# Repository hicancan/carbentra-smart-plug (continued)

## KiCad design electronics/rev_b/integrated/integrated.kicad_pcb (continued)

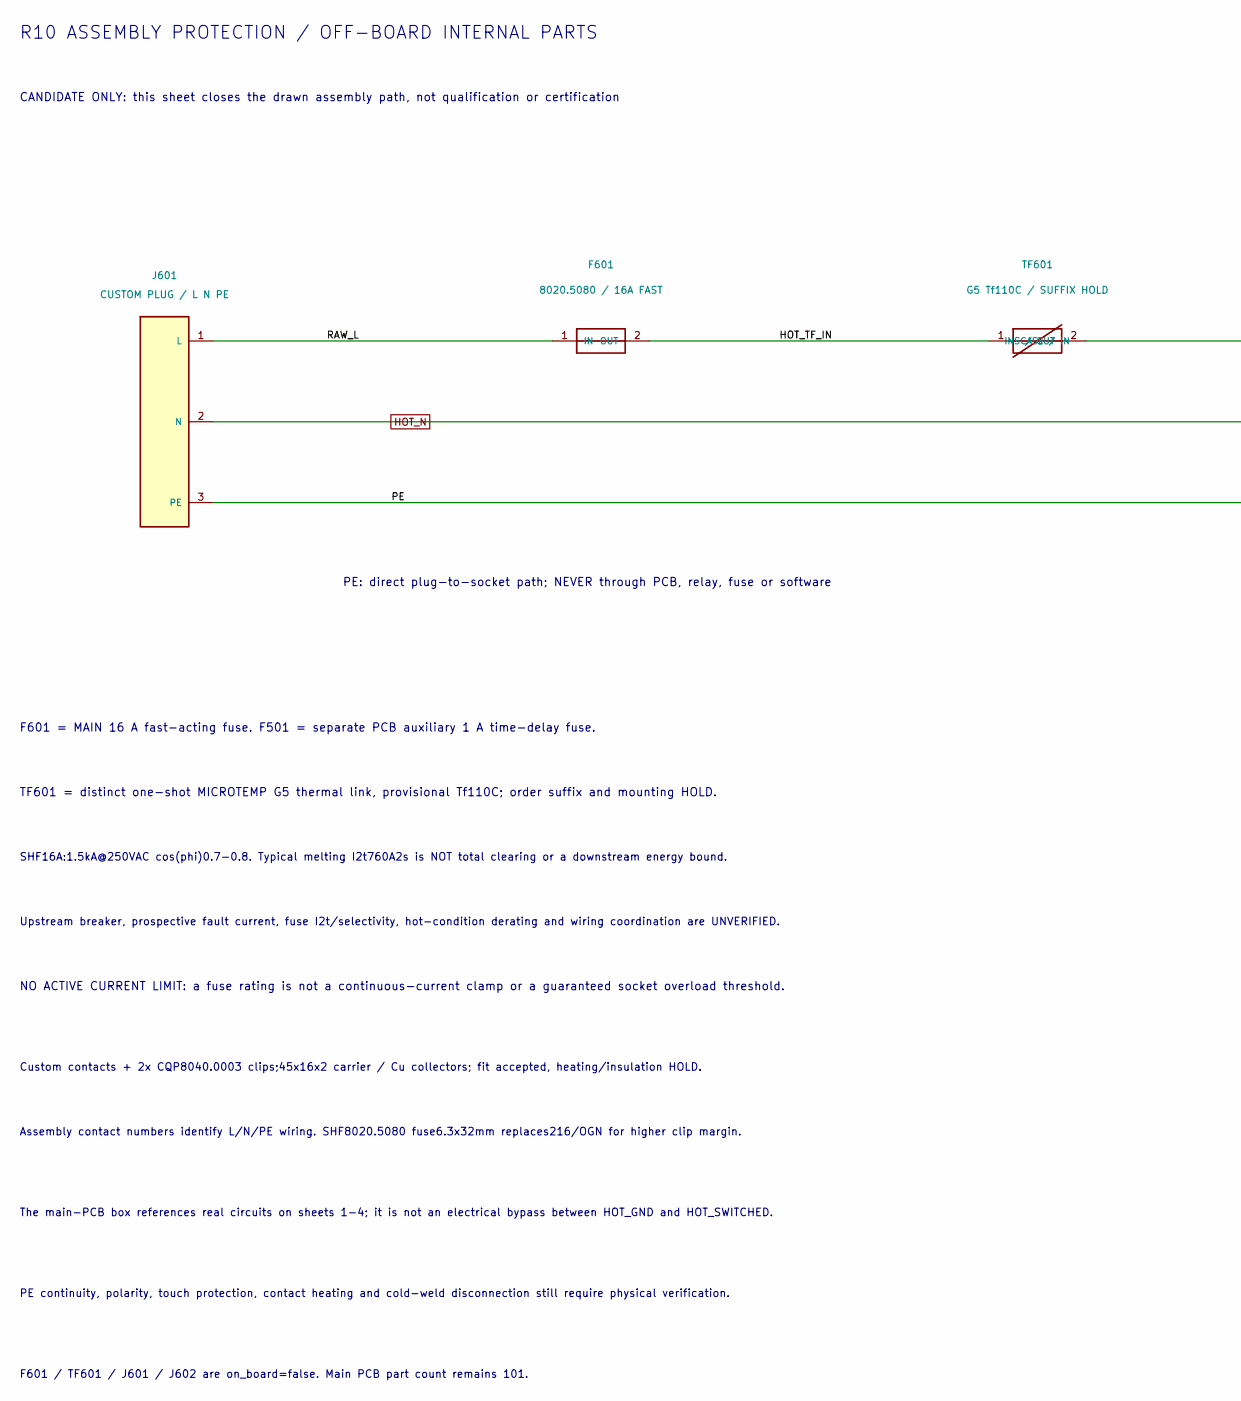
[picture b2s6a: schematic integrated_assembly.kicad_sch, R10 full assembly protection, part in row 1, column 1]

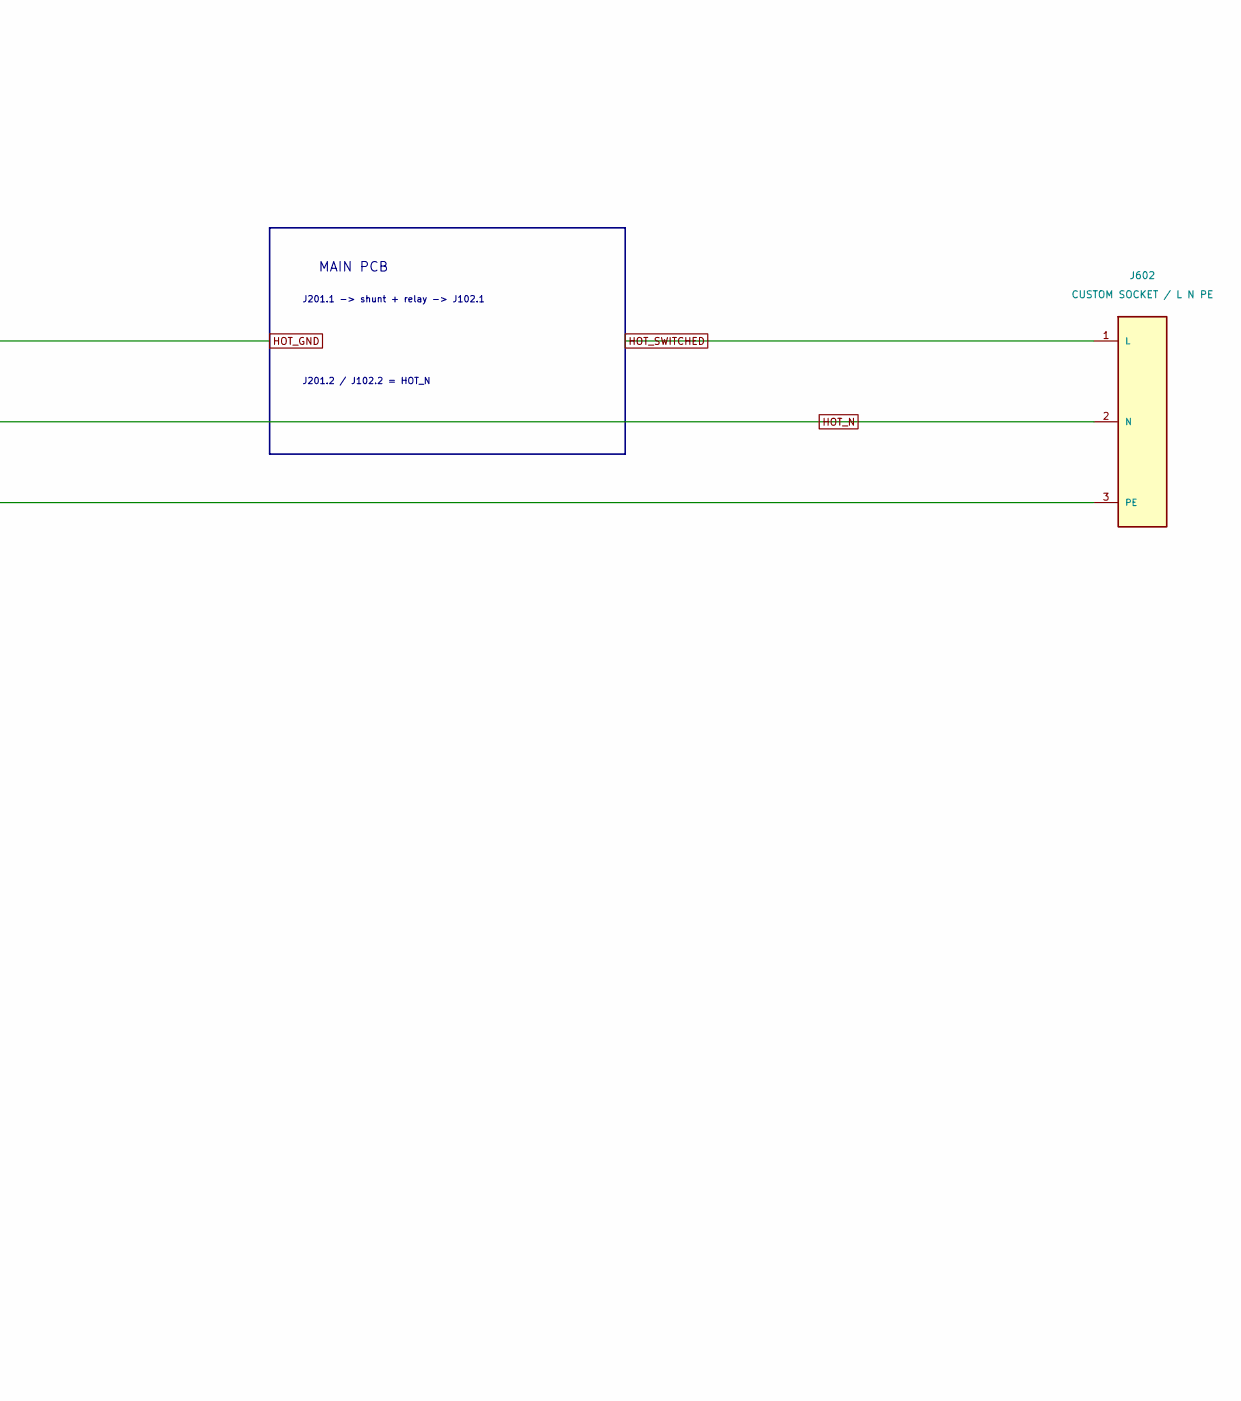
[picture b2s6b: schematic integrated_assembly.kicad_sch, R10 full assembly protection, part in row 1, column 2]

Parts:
F601: 8020.5080 / 16A FAST
J601: CUSTOM PLUG / L N PE
J602: CUSTOM SOCKET / L N PE
TF601: G5 Tf110C / SUFFIX HOLD

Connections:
unnamed: F601.1 (IN), J601.1 (L)
unnamed: F601.2 (OUT), TF601.1 (CASE / IN)
unnamed: J601.2 (N), J602.2 (N)
unnamed: J601.3 (PE), J602.3 (PE)

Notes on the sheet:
R10 ASSEMBLY PROTECTION / OFF-BOARD INTERNAL PARTS
CANDIDATE ONLY: this sheet closes the drawn assembly path, not qualification or certification
MAIN PCB
J201.1 -> shunt + relay -> J102.1
J201.2 / J102.2 = HOT_N
PE: direct plug-to-socket path; NEVER through PCB, relay, fuse or software
F601 = MAIN 16 A fast-acting fuse. F501 = separate PCB auxiliary 1 A time-delay fuse.
TF601 = distinct one-shot MICROTEMP G5 thermal link, provisional Tf110C; order suffix and mounting HOLD.
SHF16A:1.5kA@250VAC cos(phi)0.7-0.8. Typical melting I2t760A2s is NOT total clearing or a downstream energy bound.
Upstream breaker, prospective fault current, fuse I2t/selectivity, hot-condition derating and wiring coordination are UNVERIFIED.
NO ACTIVE CURRENT LIMIT: a fuse rating is not a continuous-current clamp or a guaranteed socket overload threshold.
Custom contacts + 2x CQP8040.0003 clips;45x16x2 carrier / Cu collectors; fit accepted, heating/insulation HOLD.
Assembly contact numbers identify L/N/PE wiring. SHF8020.5080 fuse6.3x32mm replaces216/OGN for higher clip margin.
The main-PCB box references real circuits on sheets 1-4; it is not an electrical bypass between HOT_GND and HOT_SWITCHED.
PE continuity, polarity, touch protection, contact heating and cold-weld disconnection still require physical verification.
F601 / TF601 / J601 / J602 are on_board=false. Main PCB part count remains 101.

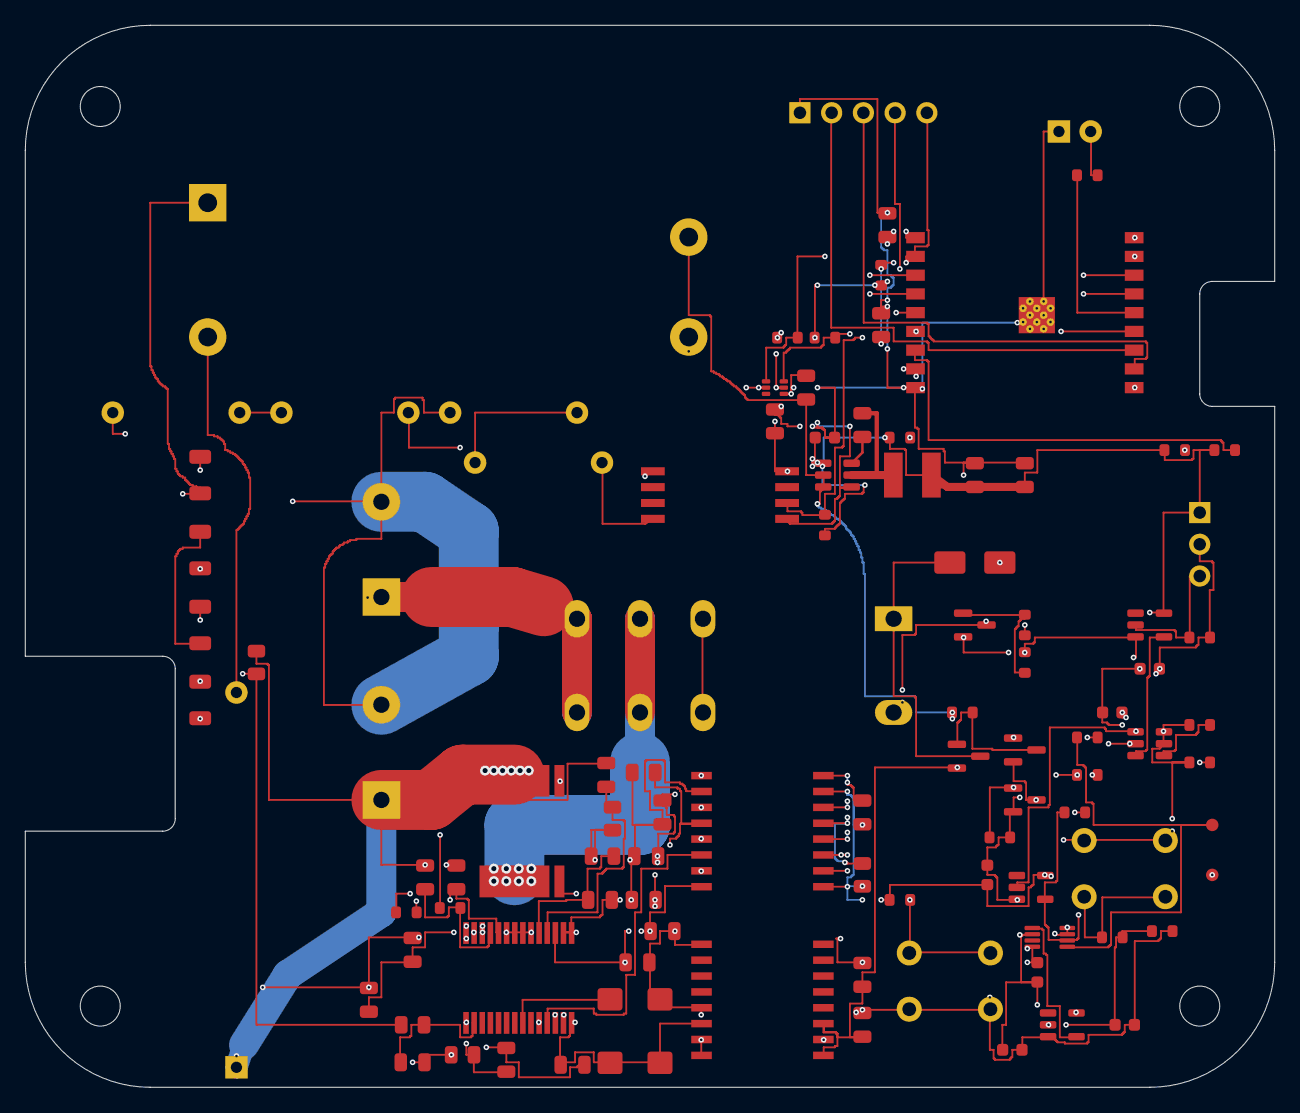
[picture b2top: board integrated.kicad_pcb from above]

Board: 4 copper layers, 100.0 x 85.0 mm, 105 parts (1 on the bottom side), 66 nets.

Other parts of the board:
H1, H2, H3, H4: MountingHole_3.2mm_M3

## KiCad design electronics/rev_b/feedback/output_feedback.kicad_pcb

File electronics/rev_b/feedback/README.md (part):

# Rev B isolated post-switch output detector

**Development candidate. Do not fabricate, connect to mains, or treat any signal as a safety indication.** Baseline EVT-A files were not edited. This is a separate, routed Rev B source module, not a certified socket or a release to energize.

## Result and interface

A 35 × 25 × 1.6 mm, two-layer module senses differential voltage at the **actual output socket L and N contacts**, after every switched pole. It uses a full-wave AC-input threshold optocoupler, four protective-impedance resistors and isolated 3.3 V logic. It needs one MCU GPIO capable of observing pulses, plus isolated power and ground. No load current is required.

- J1: L_POST, socket-side line sense only
- J2: N_POST, socket-side neutral sense only
- J3.1: +3V3_ISO; J3.2: GND_ISO; J3.3: OUTPUT_PRESENT_N
- Logic: recurring active-low pulses at twice mains frequency; LOW by itself is not a complete measurement
- Reserve **9 mm above PCB, 3 mm below PCB**, plus mating connector and wire bend/strain-relief space. These are keepout reservations, not a validated complete assembly envelope
- No protective earth conductor or load-current path is routed on this module

`output_feedback.kicad_sch`, `.kicad_pcb`, `.kicad_pro`, `.kicad_dru`, `Feedback.kicad_sym`, `Feedback.pretty/`, `pin_net_manifest.json` and `bom.csv` are the design sources. `exports/` contains schematic and board-review SVG/PNG plus the exported KiCad netlist. `scripts/build_feedback.py` rebuilds the source; `scripts/verify_feedback.py` independently checks connectivity, domain spacing and calculations. No Gerbers or fabrication package is provided.

## Circuit and pin correctness

The implemented signal path is:

L_POST → R1 33 kΩ → R2 33 kΩ → U1 pin 1 (AC1)

N_POST → R4 33 kΩ → R3 33 kΩ → U1 pin 4 (AC2)

U1 is **Broadcom ACPL-K376-560E**. Its internal bridge and input threshold controller feed the optical isolation stage. Pin 8 is isolated VCC, pin 5 isolated GND, pin 6 open-collector output. Pins 2 (DC+), 3 (DC−), and 7 (NC) are intentionally unconnected. R5, 1.8 kΩ, pulls pin 6 to isolated 3.3 V; C1, 100 nF, bypasses its isolated supply. There is no rectifier storage capacitor or mains-to-MCU resistive divider.

The source pin table was visually checked against the manufacturer functional diagram, not inferred from a generic optocoupler symbol. The four resistors are split across both input legs; **neither leg is considered touch-safe or guaranteed neutral**. Their intermediate nodes remain in the primary domain. [Broadcom datasheet, pp. 1–2](https://docs.broadcom.com/doc/AV02-2153EN)

## Why this topology

Three options were compared:

1. **H11AA1 AC phototransistor:** simple and naturally reverse-protected. However, its minimum CTR is 20% at ±10 mA, VCE = 10 V, 25°C. That is not a guarantee at ~1–2 mA, hot, aged, or saturated. At 198 VAC, obtaining 10 mA at the crest requires about 27.85 kΩ or less; at 264 VAC the resistor loss is then approximately 2.50 W before tolerance. Unnecessarily hot for a compact socket. [Vishay H11AA1 datasheet](https://www.vishay.com/docs/83608/h11aa1.pdf)
2. **Discrete 1000 V bridge + VO615A-4 phototransistor:** the 56% minimum CTR at 1 mA is useful, but it is specified at VCE = 5 V and 25°C. Multiplying that CTR into a saturated 3.3 V GPIO interface would overstate the guarantee. A transistor solution requires separate low-VCE/temperature/aging qualification or an appropriately biased comparator design. [Vishay VO615A datasheet](https://www.vishay.com/docs/81753/vo615a.pdf)
3. **Selected ACPL-K376 integrated bridge + threshold optocoupler:** threshold detection occurs before the optical transfer path, so the detector is specified by input threshold limits rather than a guessed CTR minimum. The manufacturer covers −40…105°C and includes 3.3 V operation. The component isolation ratings do not certify this PCB or assembly. [Broadcom datasheet, electrical tables](https://docs.broadcom.com/doc/AV02-2153EN)

This choice still contains a bridge and optocoupler; the bridge is integrated. There is no external diode footprint that can be assembled with the wrong AC/DC pin order.

## Component candidates and footprint basis

| Ref | Candidate | Mechanical/footprint basis |
|---|---|---|
| U1 | ACPL-K376-560E | Manufacturer SSO-8, custom `Feedback:SSO8_ACPL_K376`; body 6.807 ±0.127 × 5.850 ±0.50 mm, max height 3.307 mm; 1.27 mm pin pitch; lead span 11.50 ±0.25 mm |
| R1–R4 | Vishay PR01000103302FA100 | PR01, 33 kΩ, ±1%, 1 W at 70°C, 350 V working-voltage ceiling; custom horizontal 10.16 mm pitch, 0.9 mm drills; max body 6.5 × 2.5 mm; 0.58 ±0.05 mm leads; assembly standoff/lead forming still to qualify |
| R5 | Yageo RC0603FR-071K8L | 1.8 kΩ ±1%, 1608 metric; KiCad 0603 footprint; ordinary isolated-side pullup |
| C1 | Murata GRM188R71C104KA01D | 100 nF ±10%, X7R 16 V, 1608 metric; KiCad 0603 footprint |
| J3 | Samtec TSW-103-07-G-S | 2.54 mm pitch, three 0.635 mm square pins; vertical 1×3 header footprint; 5.84 mm mating post + 2.54 mm body = 8.38 mm nominal above board |
| J1, J2 | Internal insulated wire solder lands | Custom 1.2 mm drill / 2.4 mm copper diameter; **final wire gauge, insulation, anchoring and strain relief remain HOLD**, not a rated detachable mains connector |

U1's custom pads are 1.905 × 0.65 mm, with opposed pad centers 10.745 mm apart. The resulting pad-edge distance is 8.84 mm; the 0.65 mm width follows a practical KiCad SSO-8 land width, wider than the maximum 0.511 mm component lead. The 12.65 mm outer land span follows the manufacturer drawing. A 1 mm wide, 21 mm long routed slot under the package provides extra surface-contamination margin. **This is not permission to reduce air clearance.**

PR01 has a non-flammable coating and documented active/passive flammability tests; it is **not an agency-qualified safety fuse in this use**, and an unspecified benign open-circuit failure is not assumed. Its power/voltage/pulse/load-temperature limits all apply. [Vishay PR01 family datasheet](https://www.vishay.com/docs/28729/pr010203.pdf), [Samtec exact header](https://www.samtec.com/products/tsw-103-07-g-s), [Murata exact capacitor](https://www.murata.com/en-us/products/productdetail?partno=GRM188R71C104KA01D)

## Worst-case electrical calculations

The target is sinusoidal **198–264 VAC, 50/60 Hz**. Distorted/phase-cut waveforms require separate tests. This detector is not an RMS voltmeter. All numbers below are calculations, not bench measurements.

RΣ = 4 × 33 kΩ = 132 kΩ. Initial ±1% gives RΣ,min = 130.68 kΩ and RΣ,max = 133.32 kΩ. High-line peak is 264√2 = 373.35 V; low-line peak is 198√2 = 280.01 V.

Use the component's all-temperature AC-input limits:

- ION,max = 1.56 mA, VON,max = 5.5 V
- IOFF,max = 0.80 mA, VOFF,max = 4.42 V
- ION,min = 0.87 mA, VON,min = 4.23 V
- IOFF,min = 0.43 mA, VOFF,min = 2.87 V

These are instantaneous thresholds. Their extreme combinations are deliberately conservative; correlation is not relied on. [Broadcom datasheet, table 6](https://docs.broadcom.com/doc/AV02-2153EN)

Vsource,on,max = ION,max RΣ,max + VON,max = **213.48 V instantaneous**, or 150.95 VAC if interpreted only as a sine-wave crest threshold. That remains below the 198 VAC crest by 66.54 V. Vsource,off,max = **111.08 V instantaneous**. This broad threshold spread is why amplitude is not reconstructed from a binary reading.

Ignoring the input device's voltage drop gives conservative resistor power/current upper bounds:

- PΣ ≤ VRMS²/RΣ,min = **0.5333 W** at 264 VAC
- Ipeak ≤ √2 VRMS/RΣ,min = **2.857 mA**
- Individual resistor mismatch: Pi ≤ VRMS² Ri/(ΣRj)²; Vi,RMS ≤ VRMS Ri/ΣRj
- Exhaustive ±1% corners give **0.1347 W and 67.00 VRMS** worst for one resistor, not simply PΣ/4
- With one resistor shorted, three remain: **0.7111 W total**, **0.2386 W / 89.18 VRMS** worst remaining part, Ipeak ≤3.809 mA

An additional **±10% resistance analysis envelope** is included in `calculations.json`. This is an engineering allowance, not a manufacturer lifetime guarantee: it accommodates initial 1%, roughly 3% temperature contribution including self-heating, and the 5% endurance-test drift figure with multiplicative headroom. Real mission-life drift, enclosed thermal gradients and pulse damage must be qualified. The margin still supports the target sine-wave range; consult the machine-generated values for exact results. Expected high-line resistor heat is approximately **0.59 W maximum** within that allowance. Do not substitute four unspecified miniature chip resistors.

For one resistor open, a single gap may see the full applied voltage; do not claim the remaining series resistors divide that voltage. An optocoupler input short leaves the series impedance current-limiting; multiple resistor shorts or a carbonized PCB fault are not covered by this simple model. A normal ampere-rated socket fuse may not clear a low-current overheating fault: fuse/impedance coordination and abnormal-condition tests remain mandatory.

### Logic and pulse timing

The 1.8 kΩ pullup sinks at most approximately 1.95 mA with a 3.3 V ±5% rail and −1% resistor. A conservative 100 µA off-leakage allowance leaves at least **2.953 V** at VDD = 3.135 V and Rpullup = 1818 Ω, before host input leakage. Check the actual MCU VIH/VIL specifications, supply tracking and injection-current limits. The datasheet has 3.3 V switching characterization; its 0.4 V static VOL test is stated at VCC = 4.5 V / 4.2 mA, so **the exact 3.3 V low-state margin is still an application verification item**, not silently extrapolated into a new full-temperature guarantee.

For a sinusoid with angular frequency ω, the low pulse width is:

TLOW = [π − asin(VON/Vpeak) − asin(VOFF/Vpeak)] / ω

The high interval around a zero crossing is:

THIGH = [asin(VON/Vpeak) + asin(VOFF/Vpeak)] / ω

At initial tolerance, the shortest calculated low interval across 198–264 VAC is **4.952 ms at 60 Hz**, and the shortest high interval is **1.274 ms**. The wider resistance allowance remains comfortably millisecond-scale. Propagation delays, actual GPIO thresholds and parasitic capacitance shorten or lengthen observed intervals. Use interrupt timestamps or ≥2 ksample/s polling; do not apply a multi-millisecond hardware RC that erases zero-crossing gaps.

Recommended firmware contract:

1. Begin in UNKNOWN after power-up, brownout, reconnect or missing data
2. Accept AC_PRESENT after at least three well-formed pulse periods, expected roughly 8.33/10 ms; provisionally allow 7.5–11.5 ms for qualification, reject isolated sub-0.4 ms spikes and require both levels
3. No valid pulses for 40 ms means **NO_AC_PULSES_DETECTED**, never SAFE, DEAD, ISOLATED or RELAY_OPEN
4. A sustained LOW for 25 ms means **PRESENT_OR_STUCK_LOW / FAULT**, including possible DC/backfeed or a shorted detector output
5. For an OFF command, allow relay release/bounce/settling before comparison (provisional 100 ms); persistent qualified pulses latch an output-present-after-OFF fault, inhibit new ON commands, and request service
6. For an ON command, missing pulses means supply/contact/wiring/sensor fault or unavailable supply; do not repeatedly chatter the relay trying to diagnose it
7. Confirm these provisional windows with the chosen relay and worst-case waveform; software examples alone are not a safety mechanism

## What the signal cannot establish

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
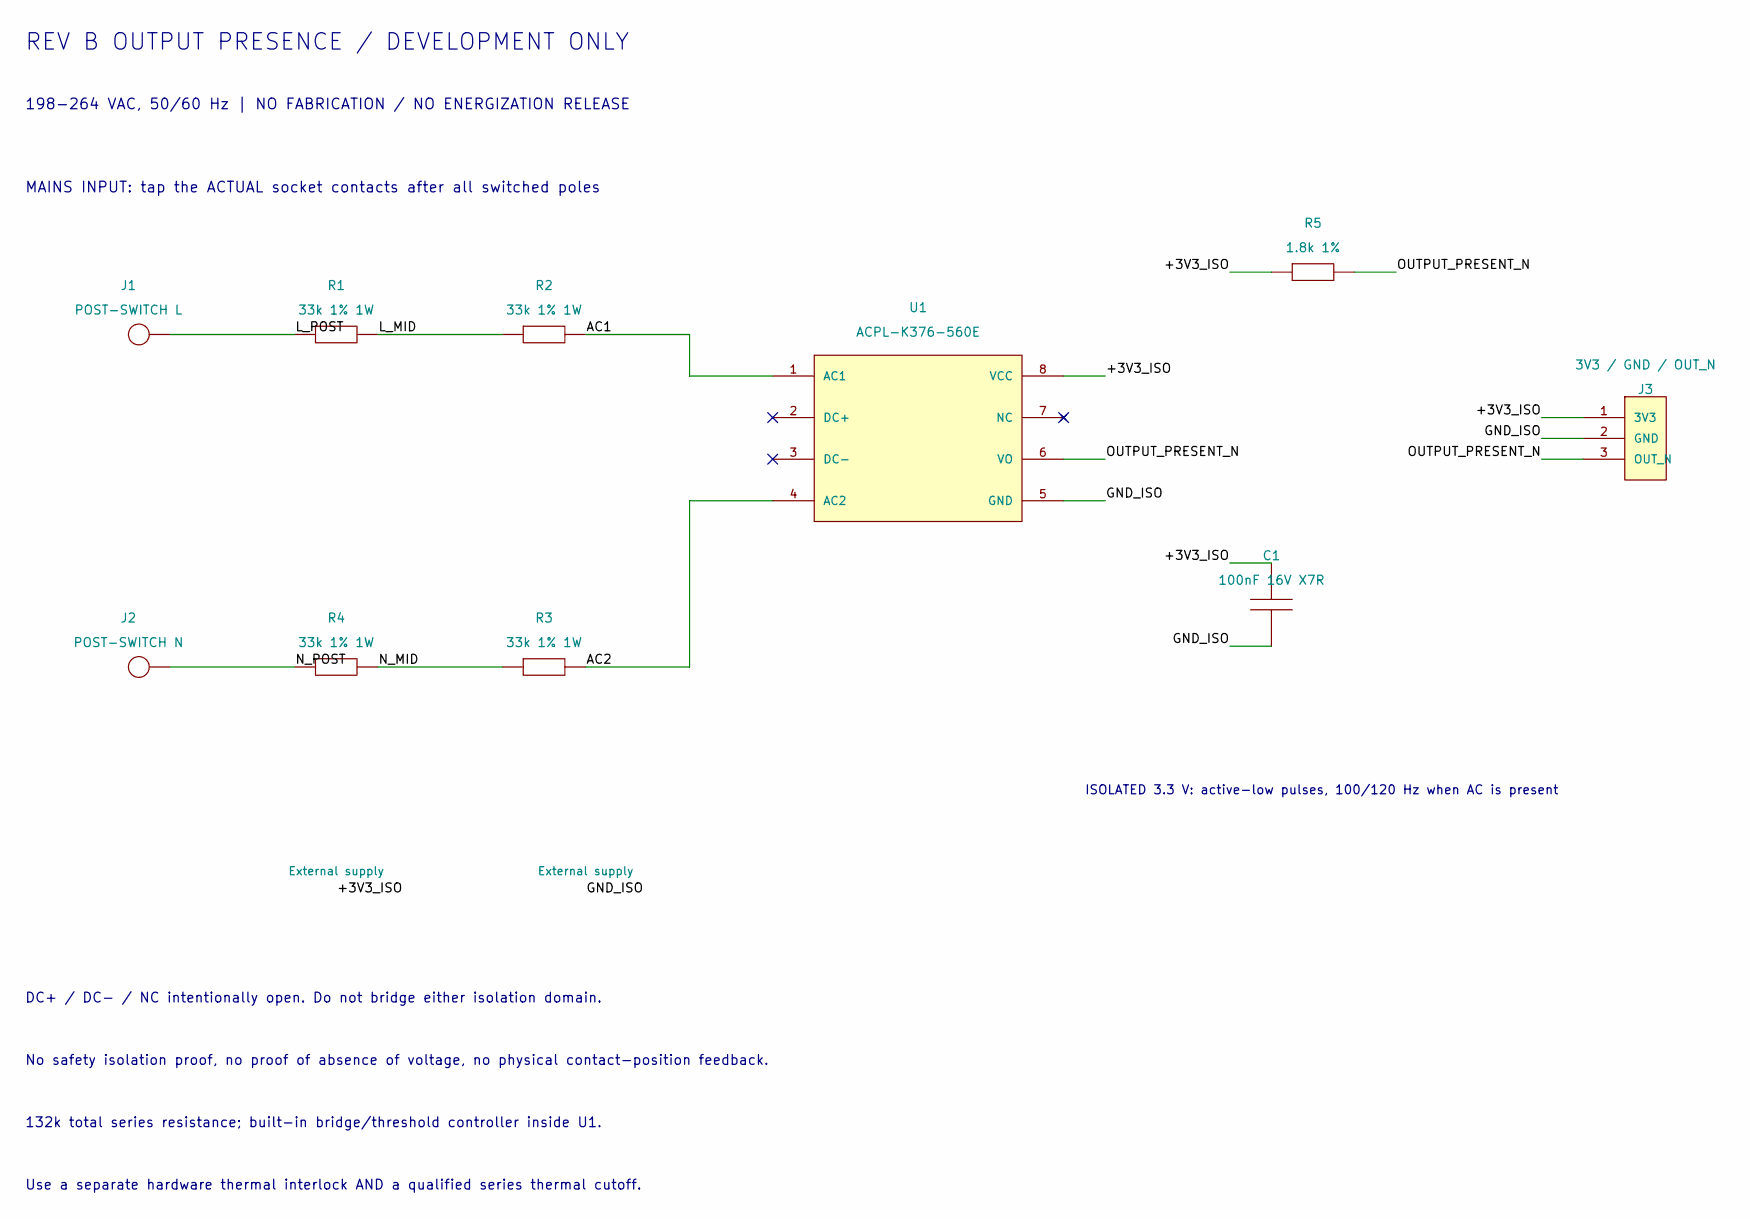
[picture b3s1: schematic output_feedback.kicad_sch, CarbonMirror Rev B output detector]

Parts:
C1: 100nF 16V X7R; C_0603_1608Metric
J1: POST-SWITCH L; Wire_Pad_1.2mm
J2: POST-SWITCH N; Wire_Pad_1.2mm
J3: 3V3 / GND / OUT_N; PinHeader_1x03_P2.54mm_Vertical
R1, R2, R3, R4: 33k 1% 1W; PR01_P10.16
R5: 1.8k 1%; R_0603_1608Metric
U1: ACPL-K376-560E; SSO8_ACPL_K376

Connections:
+3V3_ISO: C1.1, J3.1 (3V3), R5.1, U1.8 (VCC)
AC1: R2.2, U1.1 (AC1)
AC2: R3.2, U1.4 (AC2)
GND_ISO: C1.2, J3.2 (GND), U1.5 (GND)
L_MID: R1.2, R2.1
L_POST: J1.1, R1.1
N_MID: R3.1, R4.2
N_POST: J2.1, R4.1
OUTPUT_PRESENT_N: J3.3 (OUT_N), R5.2, U1.6 (VO)

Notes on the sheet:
REV B OUTPUT PRESENCE / DEVELOPMENT ONLY
198-264 VAC, 50/60 Hz | NO FABRICATION / NO ENERGIZATION RELEASE
MAINS INPUT: tap the ACTUAL socket contacts after all switched poles
ISOLATED 3.3 V: active-low pulses, 100/120 Hz when AC is present
DC+ / DC- / NC intentionally open. Do not bridge either isolation domain.
No safety isolation proof, no proof of absence of voltage, no physical contact-position feedback.
132k total series resistance; built-in bridge/threshold controller inside U1.
Use a separate hardware thermal interlock AND a qualified series thermal cutoff.

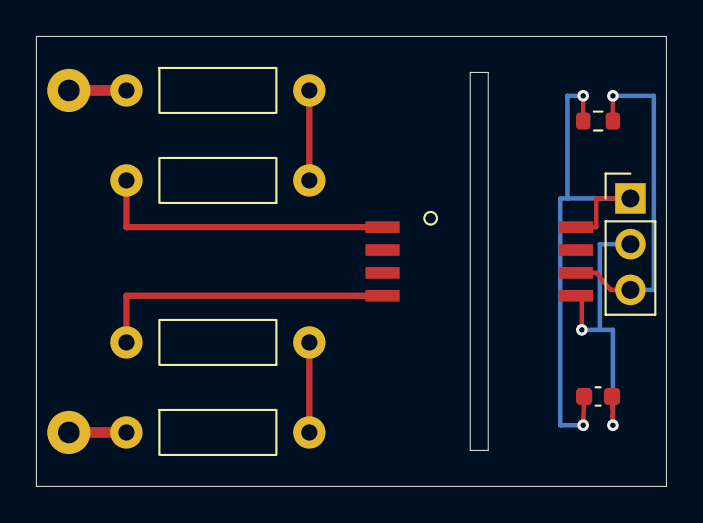
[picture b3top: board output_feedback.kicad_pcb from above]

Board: 2 copper layers, 35.0 x 25.0 mm, 10 parts (0 on the bottom side), 9 nets.

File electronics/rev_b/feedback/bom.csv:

Reference,Value,MPN candidate,Footprint,Max height mm,Source,Status
R1,33k 1% 1W,PR01000103302FA100,Feedback:PR01_P10.16,4.5,https://www.vishay.com/docs/28729/pr010203.pdf,DEVELOPMENT / VERIFY ASSEMBLY
R2,33k 1% 1W,PR01000103302FA100,Feedback:PR01_P10.16,4.5,https://www.vishay.com/docs/28729/pr010203.pdf,DEVELOPMENT / VERIFY ASSEMBLY
R3,33k 1% 1W,PR01000103302FA100,Feedback:PR01_P10.16,4.5,https://www.vishay.com/docs/28729/pr010203.pdf,DEVELOPMENT / VERIFY ASSEMBLY
R4,33k 1% 1W,PR01000103302FA100,Feedback:PR01_P10.16,4.5,https://www.vishay.com/docs/28729/pr010203.pdf,DEVELOPMENT / VERIFY ASSEMBLY
U1,ACPL-K376-560E,ACPL-K376-560E,Feedback:SSO8_ACPL_K376,3.307,https://docs.broadcom.com/doc/AV02-2153EN,DEVELOPMENT / VERIFY ASSEMBLY
R5,1.8k 1%,RC0603FR-071K8L,Resistor_SMD:R_0603_1608Metric,0.55,https://www.yageo.com/en/ProductSearch,DEVELOPMENT / VERIFY ASSEMBLY
C1,100nF 16V X7R,GRM188R71C104KA01D,Capacitor_SMD:C_0603_1608Metric,0.9,https://www.murata.com/en-us/products/productdetail?partno=G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,DEVELOPMENT / VERIFY ASSEMBLY
J1,POST-SWITCH L,Internal harness solder land; wire/strain relief HOLD,Feedback:Wire_Pad_1.2mm,4,,DEVELOPMENT / VERIFY ASSEMBLY
J2,POST-SWITCH N,Internal harness solder land; wire/strain relief HOLD,Feedback:Wire_Pad_1.2mm,4,,DEVELOPMENT / VERIFY ASSEMBLY
J3,3V3 / GND / OUT_N,TSW-103-07-G-S,Connector_PinHeader_2.54mm:PinHeader_1x03_P2.54mm_Vertical,8.38,https://www.samtec.com/products/tsw,DEVELOPMENT / VERIFY ASSEMBLY

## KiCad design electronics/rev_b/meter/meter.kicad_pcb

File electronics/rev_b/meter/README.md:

# Rev B metering daughterboard

**Development candidate. Do not fabricate for energization or connect to mains.** This revision contains a genuine schematic and fully connected PCB candidate, including the load-current shunt and both isolation barriers. Electrical continuity and DRC do not establish safety, measurement accuracy or manufacturing readiness.

## What is implemented

- 39 electrical components and four M2 mounting holes, 75 × 45 × 1.6 mm board
- ATM90E26-YU, calibrated L-only SPI metering, 8.192 MHz crystal and specified decoupling/reset/filter networks
- Bourns CSS4J-4026R-1L00FE four-terminal 1 mΩ shunt with separate force and sense pads
- Four 249 kΩ precision divider resistors, 1 kΩ lower leg and matched voltage filters
- TI ISO6741DWR default-high reinforced SPI isolation candidate
- RECOM R05CT05S-R configured for isolated 3.3 V; hot ground is deliberately connected to protected line
- Explicit 8 mm HOT-to-ISO copper rule and 3 mm neutral-sense-to-active-hot-circuit rule
- Two separated ground pours; no ground or copper plane crosses the isolation barrier

Native sources: `meter.kicad_sch`, `meter.kicad_pcb`, `meter.kicad_pro`, `meter.kicad_dru`. `circuit_manifest.json` and `bom.csv` hold pin-level design intent and sourced component candidates. `exports/meter.pdf` is the grouped schematic. STEP/FCStd/OBJ are nominal package-envelope and actual trace/via inspection models; they are not vendor detailed manufacturing solids.

## Interfaces and polarity

J1 pin2 receives the externally fused/thermally protected line. J1 pin1 supplies the relay common through the shunt. **This connector intentionally uses pin2 as the input; do not assume pin1 is input.** J2 pin1 is neutral voltage sense; J2 pin2 is unused and must not become a convenience load-current return. Neutral load current remains in the dedicated main power path.

J3 is an isolated 8-pin interface: 1=3V3, 2=GND, 3=SCLK, 4=MOSI, 5=MISO, 6=CS, 7=5V, 8=GND. The separate controller revision uses a combined 2×6 harness with these first eight logical pins and additional feedback/interlock signals. Do not connect matching physical header row positions without the harness drawing.

Hot reference is upstream line. I1P senses the downstream negative shunt drop; I1N senses upstream potential. Voltage VP samples neutral relative to upstream line, so both voltage/current polarity are inverted together and positive consumed active power is expected. Verify sign with a known resistive reference before enabling commissioning. A mistaken Kelvin lead swap must fail commissioning, not be hidden automatically.

## Layout/manufacturing assumptions

The stackup explicitly requests nominal 70 µm copper per side and a 1.6 mm finished board. The two force routes use 4.8 mm top copper, with component-pad necks and solder joints requiring thermal verification. Small signal routing uses 0.15 mm minimum clearance and 0.20 mm finished drills/0.45 mm lands at the smallest vias. Some vias lie in SMD pads: filled/capped via-in-pad processing or a reviewed escape-layout revision is required. Do not issue untreated through-vias under solderable pads.

The custom ISO6741 footprint moves lands outward to provide an 8.1 mm opposite-pad gap. The RECOM land pattern uses the manufacturer's HV option. Assembly solder-joint geometry must be reviewed against actual lead tolerances and stencil. The Bourns footprint uses separate force rectangles and sense tabs based on the published land-pattern dimensions; optional inward sense-routing extensions are omitted. First-article land-pattern verification remains mandatory.

8 mm is a design target, not a declaration of conformity. Applicable product standard, pollution degree, overvoltage category, material group, altitude, working voltage, enclosure barriers, conductive fasteners and wire routing must be independently assessed. Reinforced component ratings do not automatically qualify the board or enclosure.

The oscillator nets currently use multiple layers. Startup margin, drive level, effective crystal load and immunity near the converter need measurement; the 27 pF capacitors assume approximately 4.5 pF total stray loading for an 18 pF crystal. No measured clock or EMC claim is made.

## Validation and remaining gates

Actual KiCad reports are in `validation/`. `net_pin_consistency.json` checks every assigned schematic pin against the exported netlist and PCB; this catches accidental graphical wire joins. `geometry.json` checks model shape validity. The native board is authoritative; no unrouted airwire is represented as a trace in the model.

Required before energization: qualified mains protection coordination, prospective short-circuit current and fuse I²t, shunt fault-pulse/solder survival, all conductor/terminal temperature rises, insulation tests, leakage/touch-current and creepage review, EMI/surge/EFT tests, calibrated metering validation, mechanical harness/lead clearances and formal electrical sign-off. The standard meter cannot interrupt a short circuit and may saturate during appliance inrush. Output-voltage feedback and thermal interruption are separate Rev B boards.

See `../FIRMWARE_CONTRACT.md` for the verified register protocol and calibration-required startup path. No calibration values, firmware commissioning or physical measurements are fabricated here.

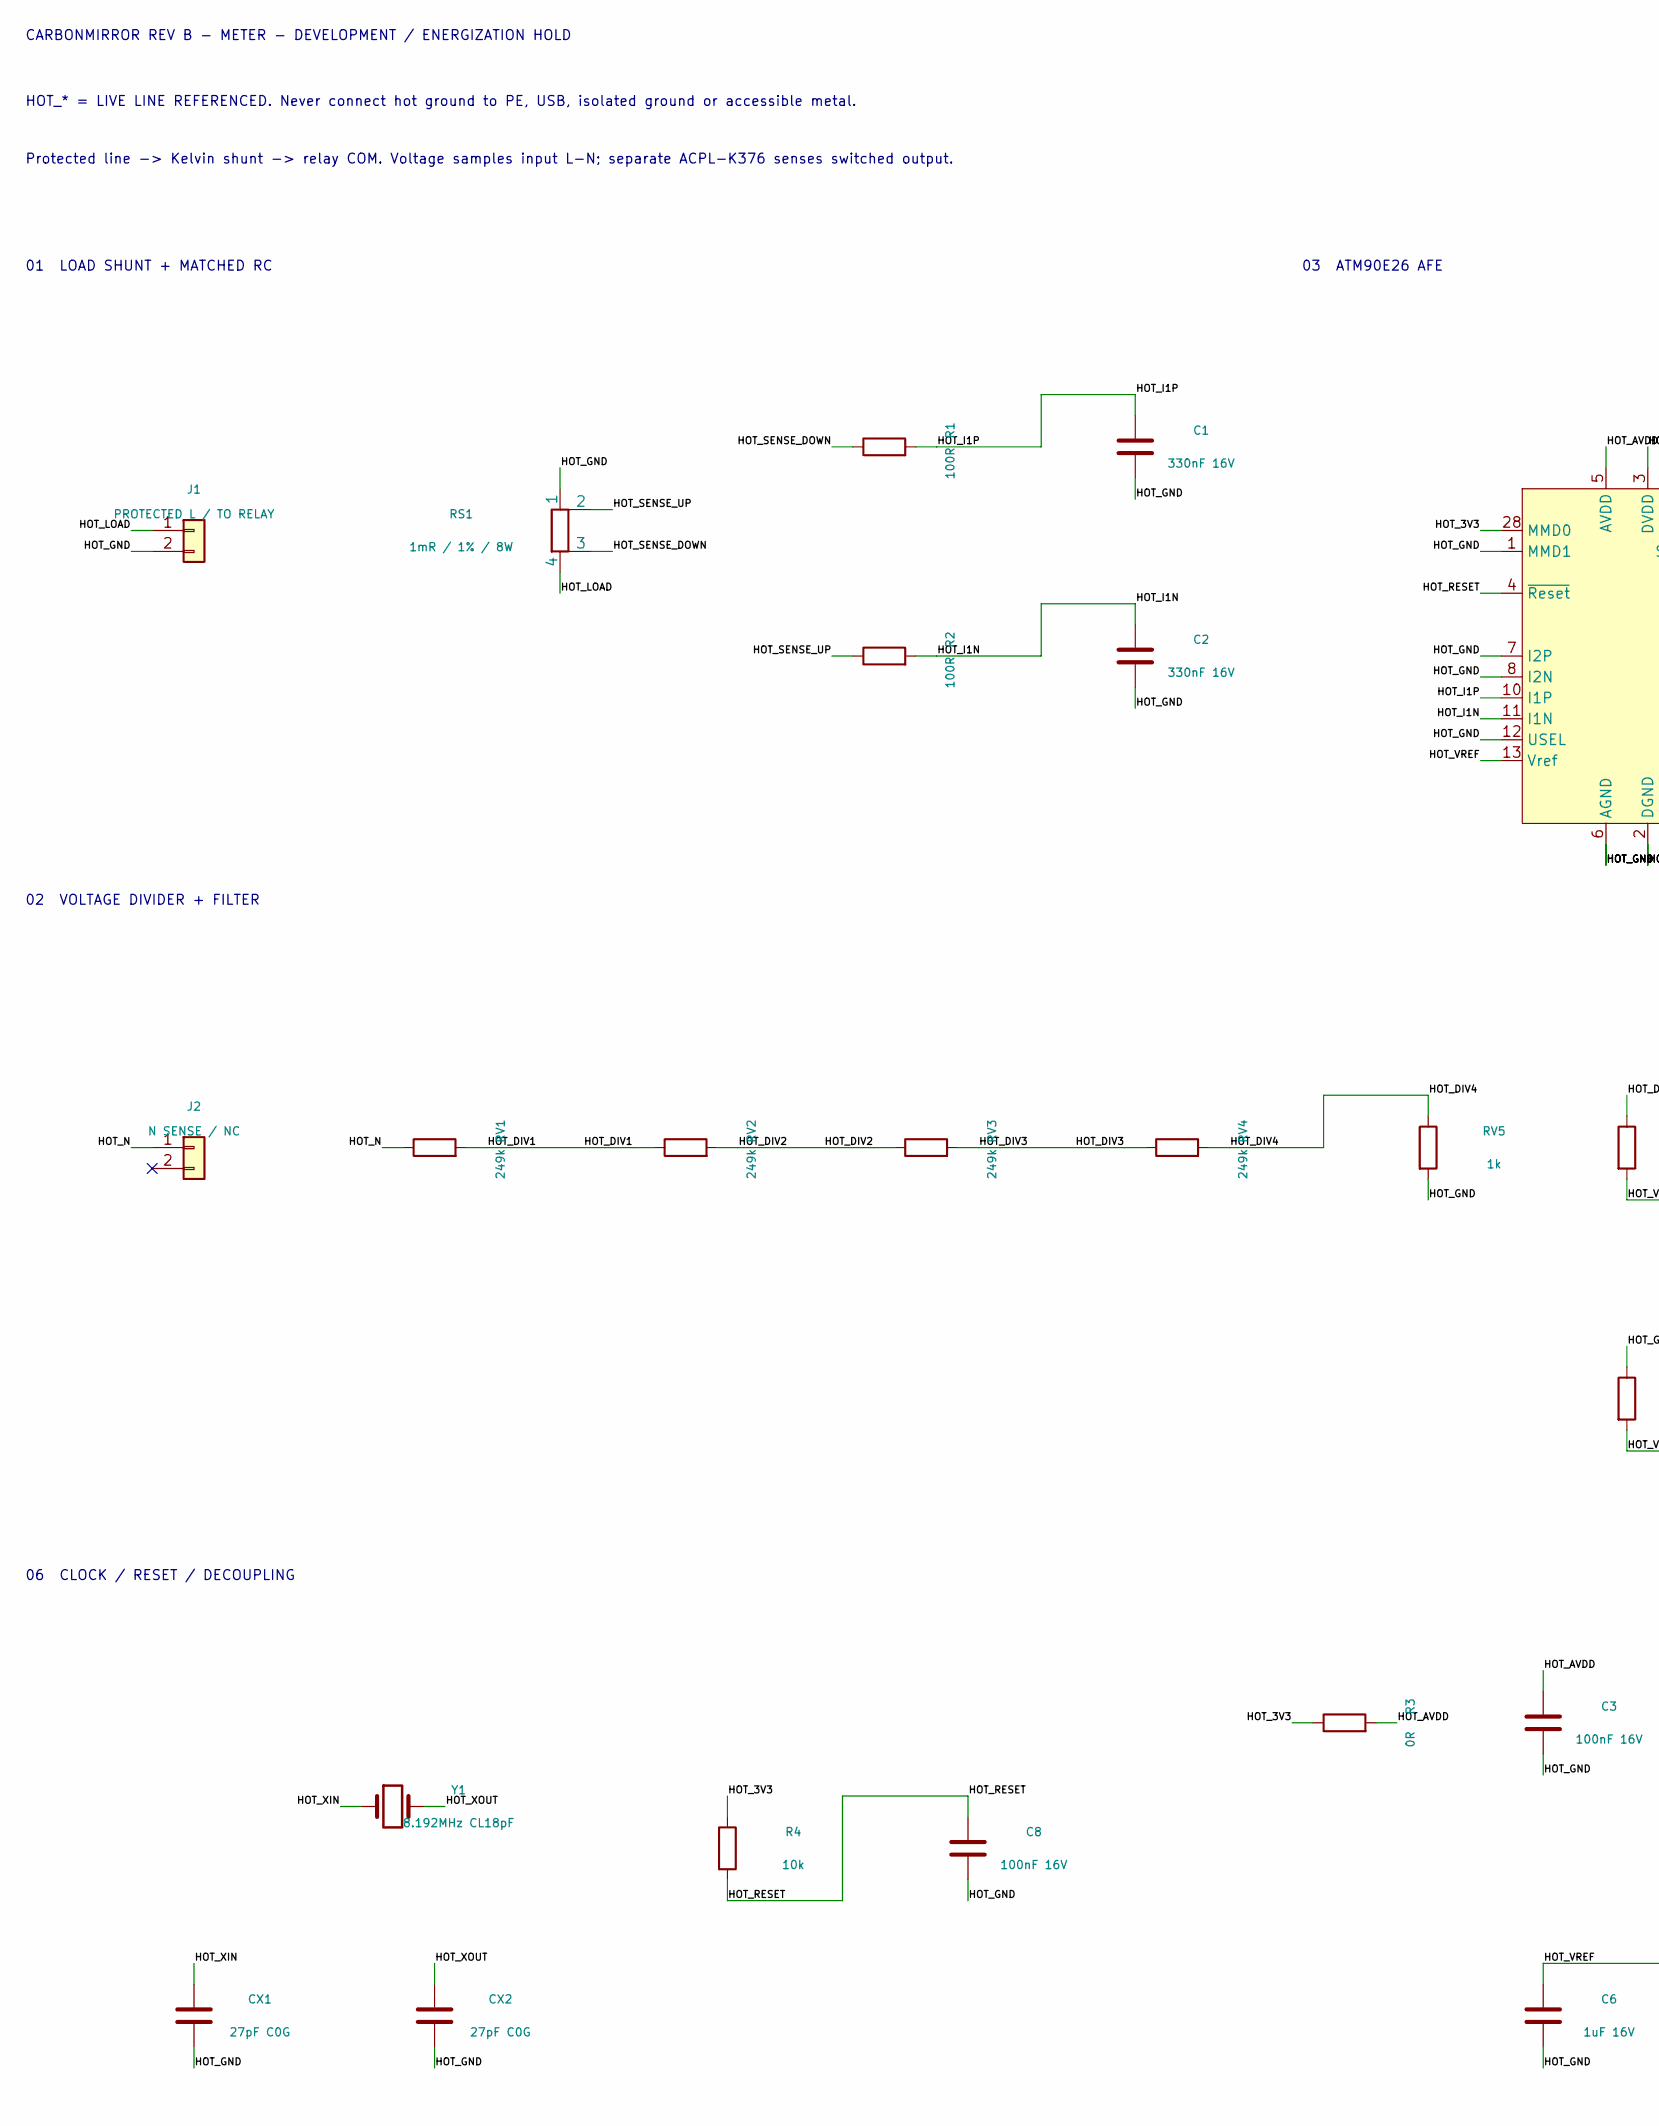
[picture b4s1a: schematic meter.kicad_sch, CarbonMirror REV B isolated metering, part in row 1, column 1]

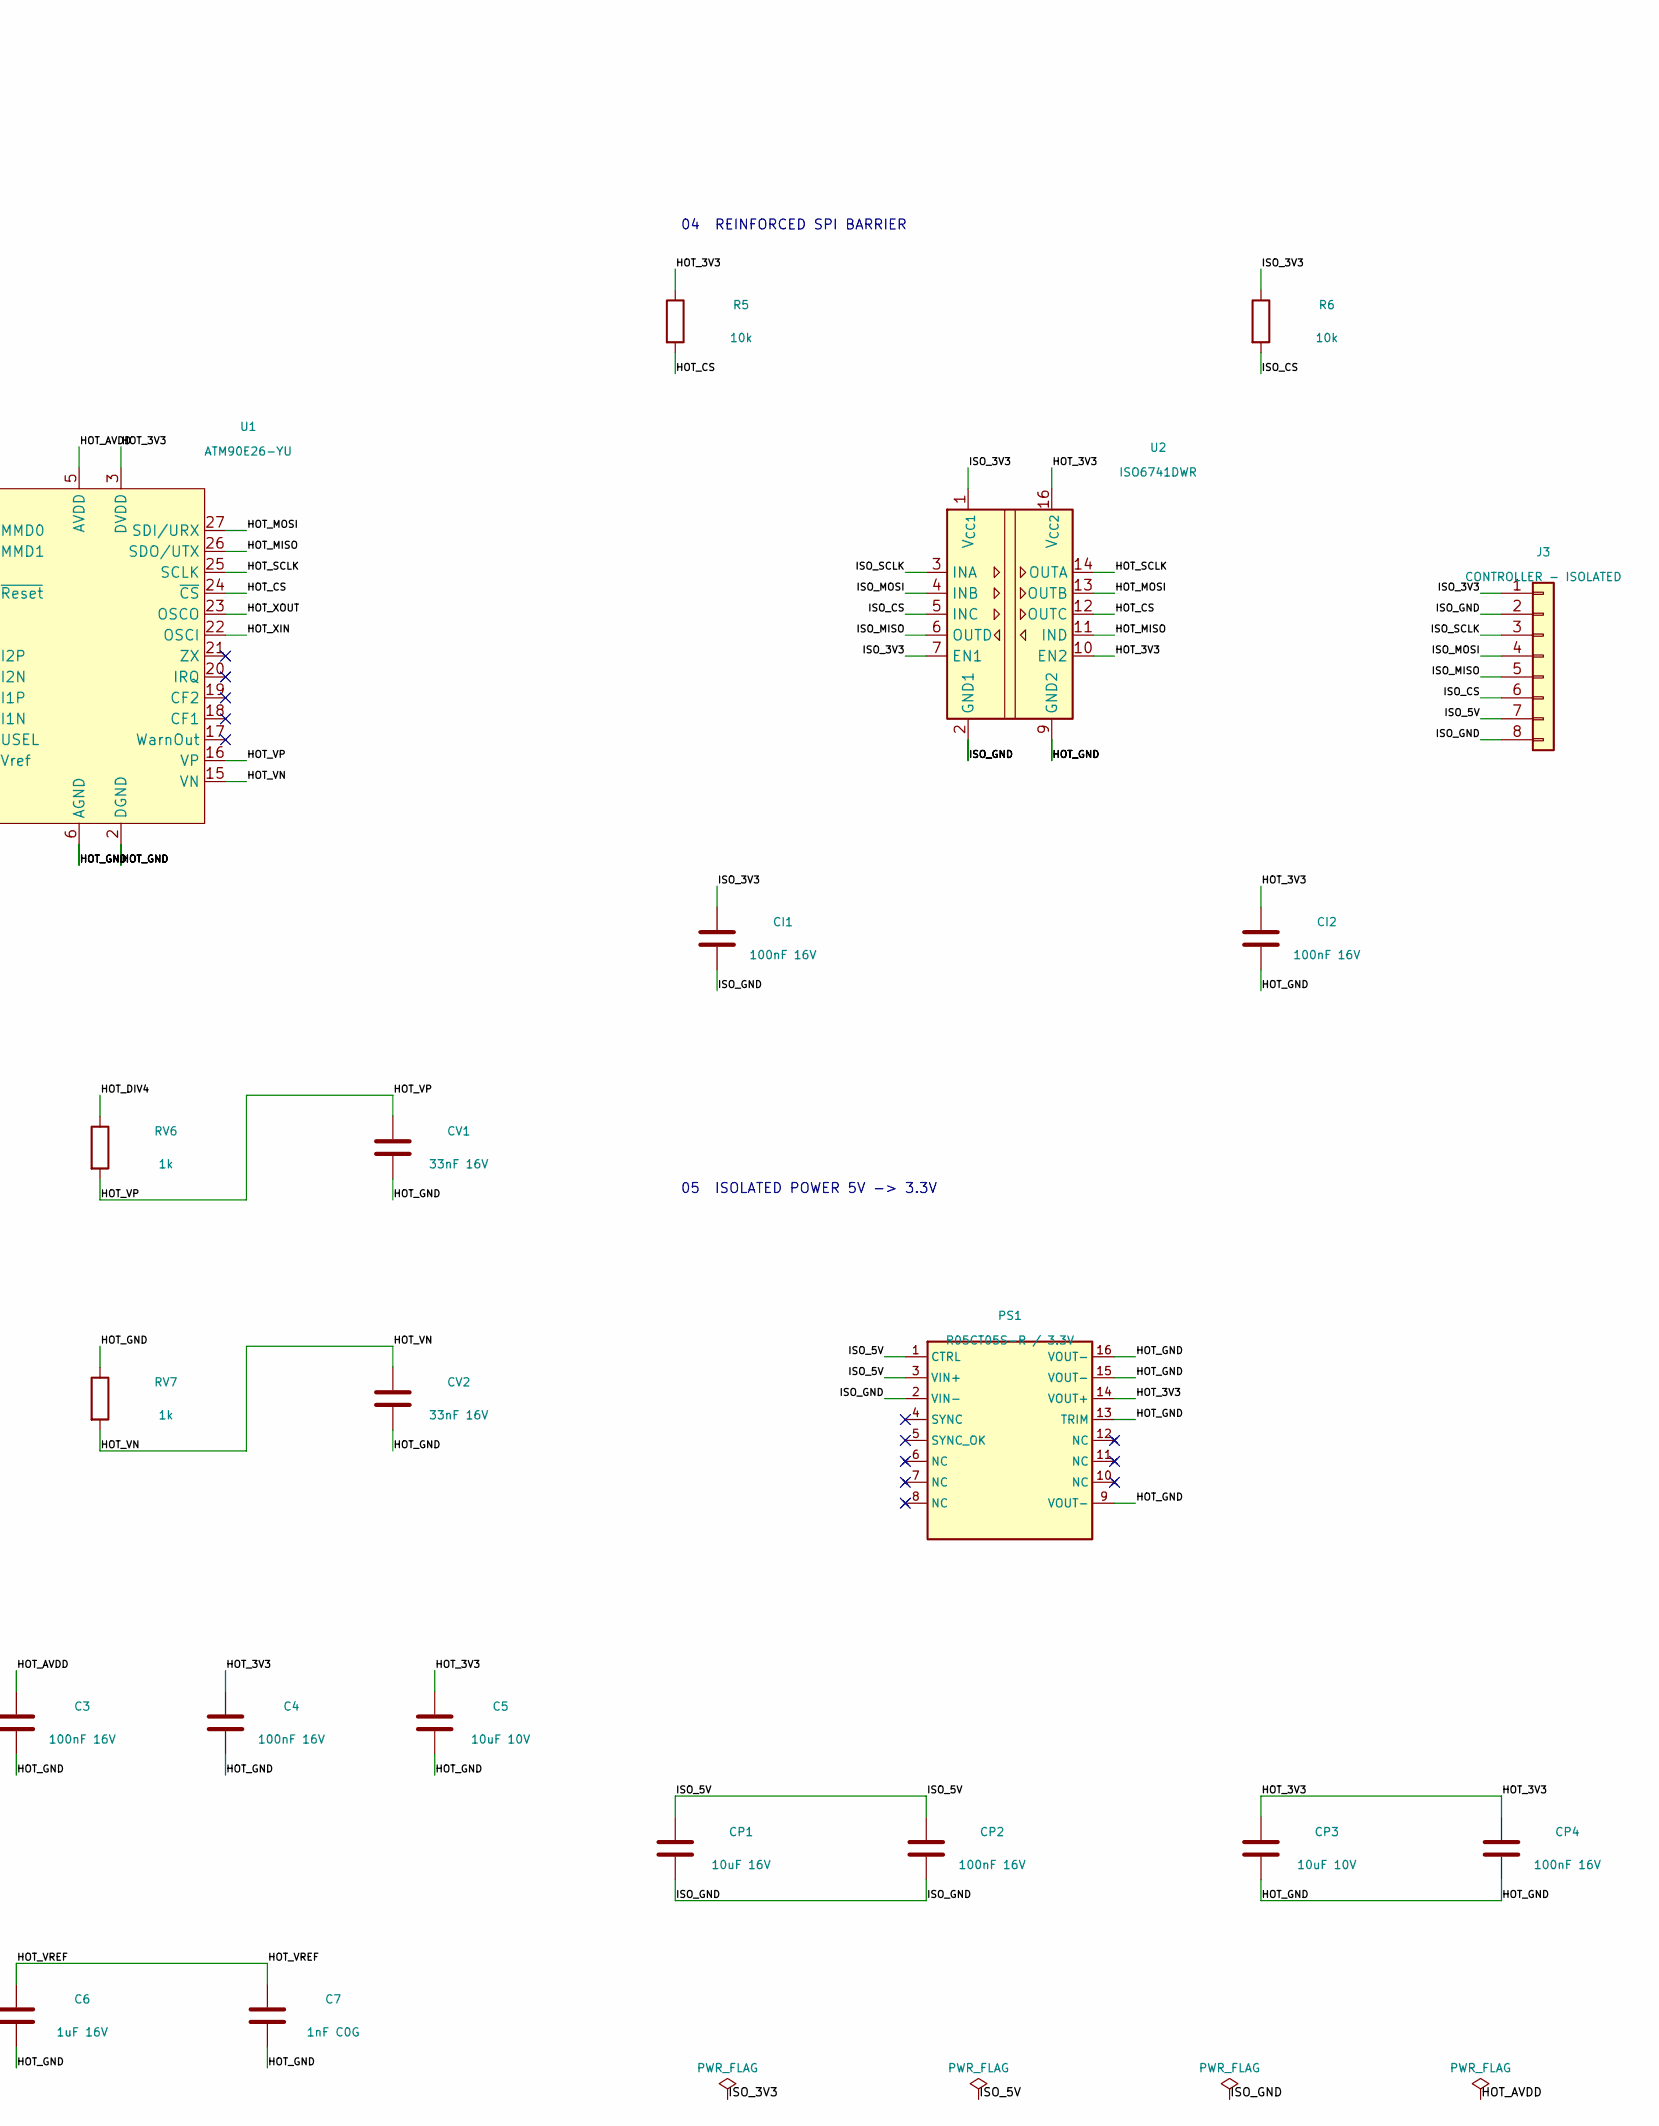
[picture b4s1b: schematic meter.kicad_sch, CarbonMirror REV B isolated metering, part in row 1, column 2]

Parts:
C1, C2: 330nF 16V; C_0805_2012Metric
C3, C4, C8: 100nF 16V; C_0805_2012Metric
C5: 10uF 10V; C_0805_2012Metric
C6: 1uF 16V; C_0805_2012Metric
C7: 1nF C0G; C_0805_2012Metric
CI1, CI2: 100nF 16V; C_0805_2012Metric
CP1: 10uF 16V; C_0805_2012Metric
CP2, CP4: 100nF 16V; C_0805_2012Metric
CP3: 10uF 10V; C_0805_2012Metric
CV1, CV2: 33nF 16V; C_0805_2012Metric
CX1, CX2: 27pF C0G; C_0805_2012Metric
J1: PROTECTED L / TO RELAY; TerminalBlock_Phoenix_MKDS-3-2-5.08_1x02_P5.08mm_Horizontal
J2: N SENSE / NC; TerminalBlock_Phoenix_MKDS-3-2-5.08_1x02_P5.08mm_Horizontal
J3: CONTROLLER - ISOLATED; PinHeader_1x08_P2.54mm_Vertical
PS1: R05CT05S-R / 3.3V; R05CT05S_8p1
R1, R2: 100R; R_0805_2012Metric
R3: 0R; R_0805_2012Metric
R4, R5, R6: 10k; R_0805_2012Metric
RS1: 1mR / 1% / 8W; CSS4J_4026
RV1, RV2, RV3, RV4: 249k; R_1206_3216Metric
RV5, RV6, RV7: 1k; R_0805_2012Metric
U1: ATM90E26-YU; SSOP-28_5.3x10.2mm_P0.65mm
U2: ISO6741DWR; ISO6741_DW_8p1
Y1: 8.192MHz CL18pF; Crystal_SMD_HC49-SD

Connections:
HOT_3V3: C4.1, C5.1, CI2.1, CP3.1, CP4.1, PS1.14 (VOUT+), R3.1, R4.1, R5.1, U1.3 (DVDD), U1.28 (MMD0), U2.10 (EN2), U2.16 (V_{CC2})
HOT_AVDD: C3.1, R3.2, U1.5 (AVDD)
HOT_CS: R5.2, U1.24 (~CS), U2.12 (OUTC)
HOT_DIV1: RV1.2, RV2.1
HOT_DIV2: RV2.2, RV3.1
HOT_DIV3: RV3.2, RV4.1
HOT_DIV4: RV4.2, RV5.1, RV6.1
HOT_GND: C1.2, C2.2, C3.2, C4.2, C5.2, C6.2, C7.2, C8.2, CI2.2, CP3.2, CP4.2, CV1.2, CV2.2, CX1.2, CX2.2, J1.2, PS1.9 (VOUT-), PS1.13 (TRIM), PS1.15 (VOUT-), PS1.16 (VOUT-), RS1.1, RV5.2, RV7.1, U1.1 (MMD1), U1.2 (DGND), U1.6 (AGND), U1.7 (I2P), U1.8 (I2N), U1.9 (DGND), U1.12 (USEL), U1.14 (AGND), U2.9 (GND2), U2.15 (GND2)
HOT_I1N: C2.1, R2.2, U1.11 (I1N)
HOT_I1P: C1.1, R1.2, U1.10 (I1P)
HOT_LOAD: J1.1, RS1.4
HOT_MISO: U1.26 (SDO/UTX), U2.11 (IND)
HOT_MOSI: U1.27 (SDI/URX), U2.13 (OUTB)
HOT_N: J2.1, RV1.1
HOT_RESET: C8.1, R4.2, U1.4 (~Reset)
HOT_SCLK: U1.25 (SCLK), U2.14 (OUTA)
HOT_SENSE_DOWN: R1.1, RS1.3
HOT_SENSE_UP: R2.1, RS1.2
HOT_VN: CV2.1, RV7.2, U1.15 (VN)
HOT_VP: CV1.1, RV6.2, U1.16 (VP)
HOT_VREF: C6.1, C7.1, U1.13 (Vref)
HOT_XIN: CX1.1, U1.22 (OSCI), Y1.1
HOT_XOUT: CX2.1, U1.23 (OSCO), Y1.2
ISO_3V3: CI1.1, J3.1, R6.1, U2.1 (V_{CC1}), U2.7 (EN1)
ISO_5V: CP1.1, CP2.1, J3.7, PS1.1 (CTRL), PS1.3 (VIN+)
ISO_CS: J3.6, R6.2, U2.5 (INC)
ISO_GND: CI1.2, CP1.2, CP2.2, J3.2, J3.8, PS1.2 (VIN-), U2.2 (GND1), U2.8 (GND1)
ISO_MISO: J3.5, U2.6 (OUTD)
ISO_MOSI: J3.4, U2.4 (INB)
ISO_SCLK: J3.3, U2.3 (INA)

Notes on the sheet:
CARBONMIRROR REV B - METER - DEVELOPMENT / ENERGIZATION HOLD
HOT_* = LIVE LINE REFERENCED. Never connect hot ground to PE, USB, isolated ground or accessible metal.
Protected line -> Kelvin shunt -> relay COM. Voltage samples input L-N; separate ACPL-K376 senses switched output.
01 LOAD SHUNT + MATCHED RC
02 VOLTAGE DIVIDER + FILTER
03 ATM90E26 AFE
04 REINFORCED SPI BARRIER
05 ISOLATED POWER 5V -> 3.3V
06 CLOCK / RESET / DECOUPLING
